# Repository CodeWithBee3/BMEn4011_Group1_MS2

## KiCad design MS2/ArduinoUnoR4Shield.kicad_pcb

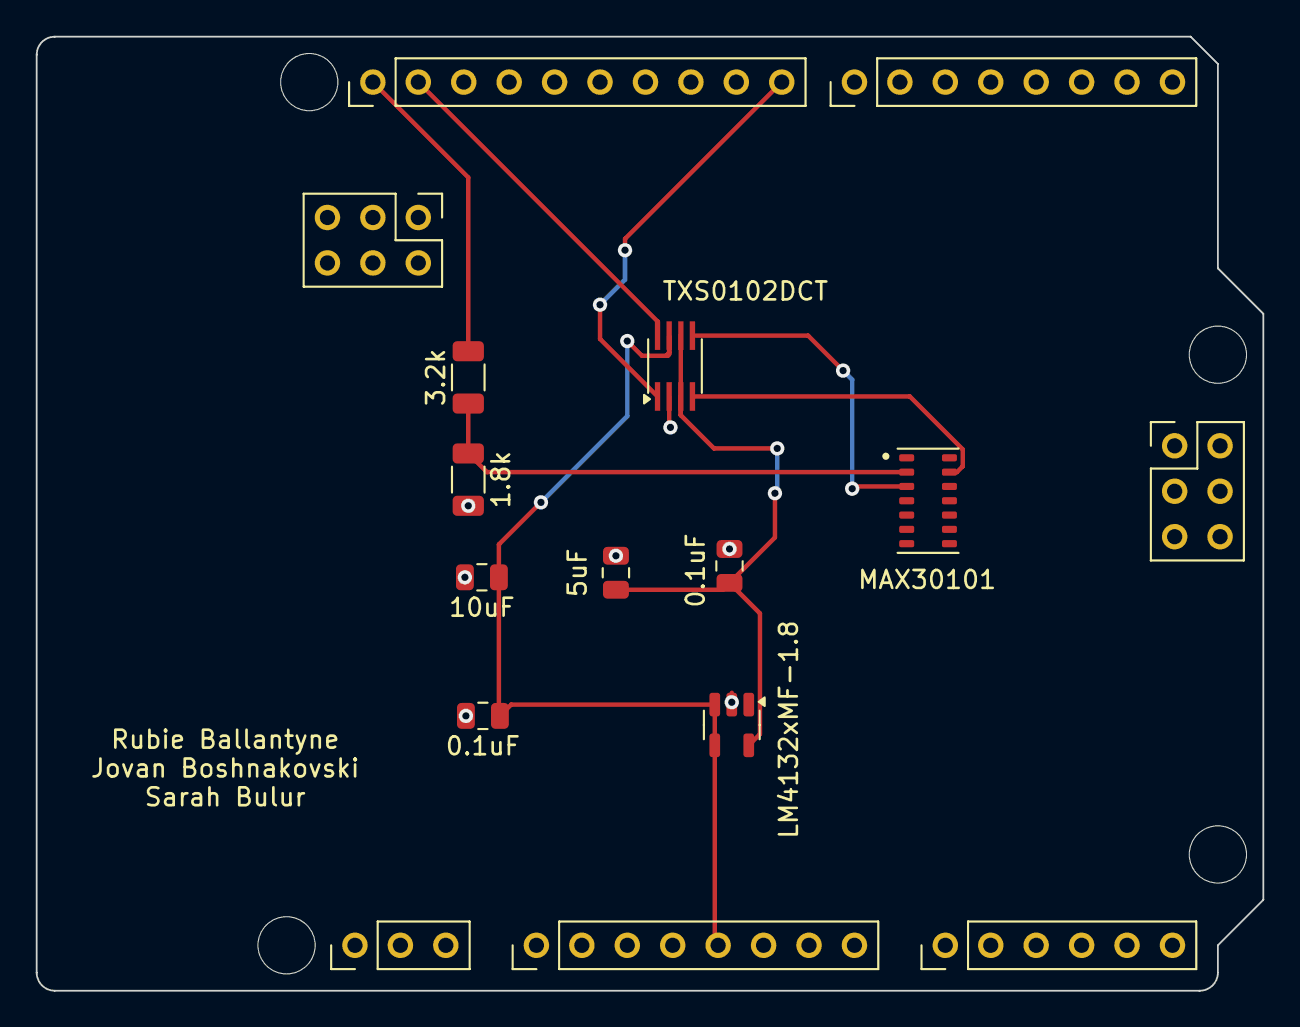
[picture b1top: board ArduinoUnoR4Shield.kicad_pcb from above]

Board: 2 copper layers, 68.6 x 53.3 mm, 20 parts (0 on the bottom side), 9 nets.

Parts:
0.1uF: 0.1uF; C_0805_2012Metric
10uF: 10uF; C_0805_2012Metric
C2: 5uF; C_0805_2012Metric
C4: 0.1uF; C_0805_2012Metric
H1: MountingHole1; Arduino_MountingHole
H2: MountingHole2; Arduino_MountingHole
H3: MountingHole3; Arduino_MountingHole
H4: MountingHole4; Arduino_MountingHole
LM4132xMF-1.8: LM4132xMF-1.8; SOT-23-5
MAX30101: PSON80P560X330X165-14N
R1: 3.2k; R_1206_3216Metric
R2: 1.8k; R_1206_3216Metric
U1: OFF; Arduino_PinSocket_1x03_P2.54mm_Vertical
U2: Analog_1; Arduino_PinSocket_1x08_P2.54mm_Vertical
U3: Analog_2; Arduino_PinSocket_1x06_P2.54mm_Vertical
U4: ESP32-S3; Arduino_PinSocket_2x03_P2.54mm_Vertical
U5: ICSP; Arduino_PinSocket_2x03_P2.54mm_Vertical
U6: Digital_1; Arduino_PinSocket_1x10_P2.54mm_Vertical
U7: Digital_2; Arduino_PinSocket_1x08_P2.54mm_Vertical
U9: TXS0102DCT; SSOP-8_2.95x2.8mm_P0.65mm

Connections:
GND: 0.1uF.2, 10uF.2, C2.2, C4.1, LM4132xMF-1.8.2 (GND), R2.1, U6.4 (GND), U9.2 (GND)
unnamed: U6.10 (D8), U9.1 (B2)
unnamed: R1.1, U6.1 (SCL)
unnamed: U6.2 (SDA), U9.8 (B1)
unnamed: MAX30101.13 (INT), U9.4 (A2)
unnamed: MAX30101.2 (SCL), R1.2, R2.2
unnamed: MAX30101.3 (SDA), U9.5 (A1)
unnamed: 0.1uF.1, 10uF.1, LM4132xMF-1.8.3 (EN), LM4132xMF-1.8.4 (VIN), U2.5 (+5V), U9.7 (VCCB)
unnamed: C2.1, C4.2, LM4132xMF-1.8.5 (VREF), U9.3 (VCCA), U9.6 (OE)
